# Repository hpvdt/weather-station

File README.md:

# weather-station
Weather station project

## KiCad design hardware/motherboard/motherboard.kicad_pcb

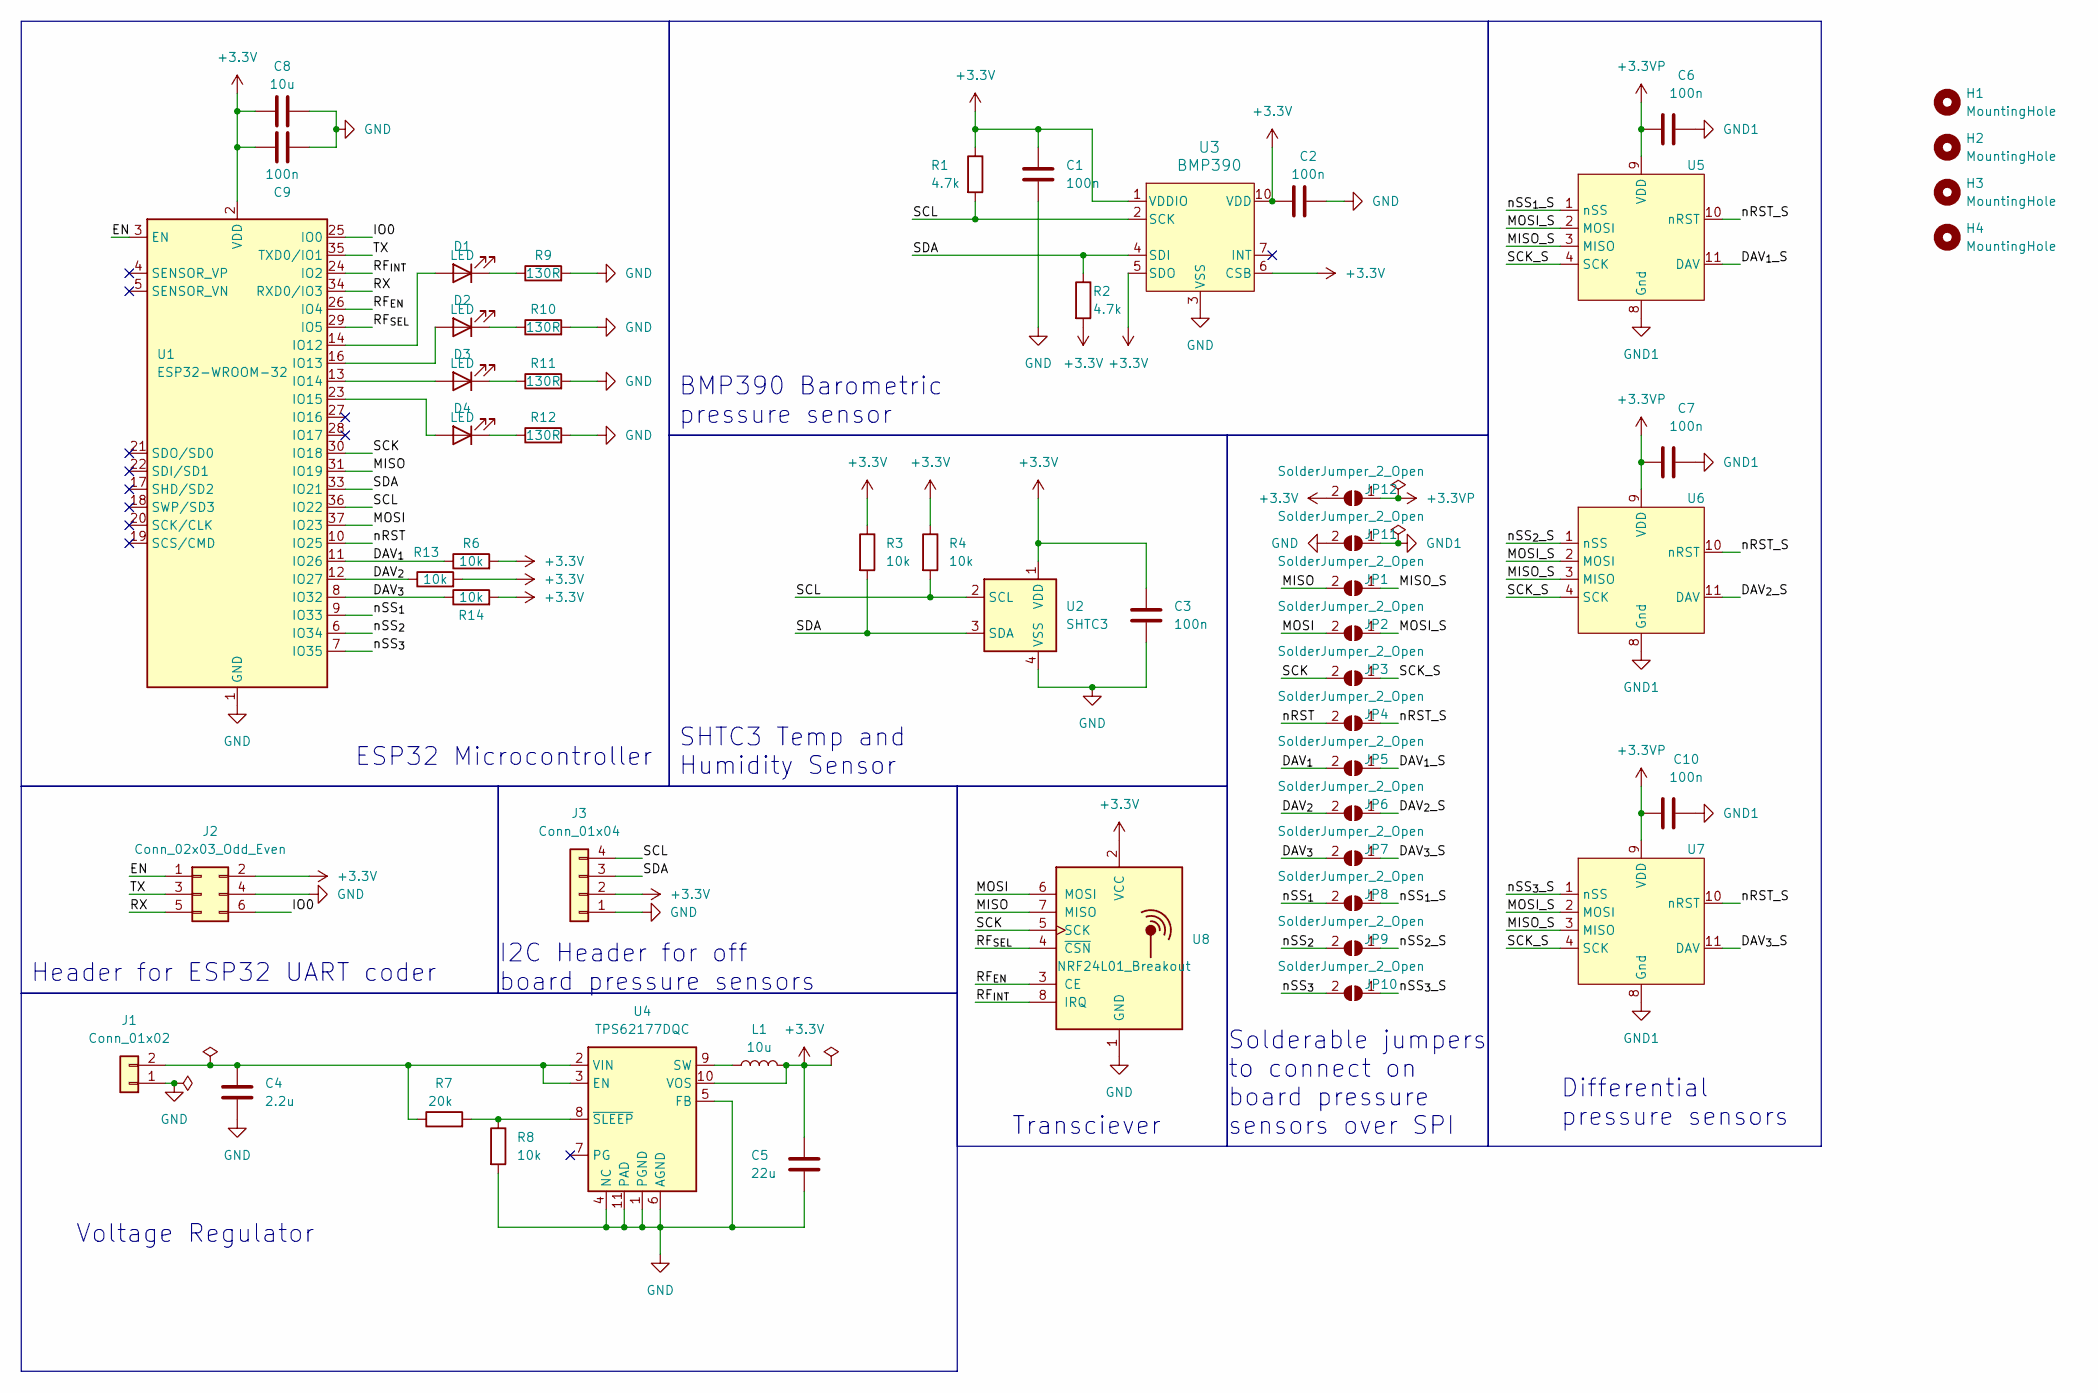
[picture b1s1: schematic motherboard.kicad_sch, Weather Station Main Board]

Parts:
C1, C2, C3, C6, C7, C9, C10: 100n; C_0603_1608Metric
C4: 2.2u; C_0603_1608Metric
C5: 22u; C_0805_2012Metric
C8: 10u; C_0805_2012Metric
D1, D2, D3, D4: LED; LED_0805_2012Metric
H1, H2, H3, H4: MountingHole; MountingHole_3mm
J1: Conn_01x02; AMASS_XT60-F_1x02_P7.20mm_Vertical
J2: Conn_02x03_Odd_Even; IDC-Header_2x03_P2.54mm_Vertical
J3: Conn_01x04; PinSocket_1x04_P2.54mm_Vertical
JP1, JP2, JP3, JP4, JP5, JP6, JP7, JP8, JP9, JP10, JP11, JP12: SolderJumper_2_Open; SolderJumper-2_P1.3mm_Open_RoundedPad1.0x1.5mm
L1: 10u; L_Taiyo-Yuden_MD-4040
R1, R2: 4.7k; R_0603_1608Metric
R3, R4, R6, R8, R13, R14: 10k; R_0603_1608Metric
R7: 20k; R_0603_1608Metric
R9, R10, R11, R12: 130R; R_0603_1608Metric
U1: ESP32-WROOM-32; ESP32-WROOM-32D
U2: SHTC3; Sensirion_DFN-4-1EP_2x2mm_P1mm_EP0.7x1.6mm
U3: BMP390; LGA10_BMP390_BOS
U4: TPS62177DQC; WSON-10-1EP_2x3mm_P0.5mm_EP0.84x2.4mm_ThermalVias
U5, U6, U7: HV120SM02C
U8: NRF24L01_Breakout; nRF24L01_Breakout

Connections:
+3.3V: C1.1, C2.1, C3.1, C5.1, C8.2, C9.2, J2.2, J3.2, JP12.2 (B), L1.2, R1.1, R2.2, R3.1, R4.1, R6.2, R13.2, R14.2, U1.2 (VDD), U2.1 (VDD), U3.1 (VDDIO), U3.5 (SDO), U3.6 (CSB), U3.10 (VDD), U4.10 (VOS), U8.2 (VCC)
+3.3VP: C6.1, C7.1, C10.1, JP12.1 (A), U5.9 (VDD), U6.9 (VDD), U7.9 (VDD)
/DAV_{1}: JP5.2 (B), R6.1, U1.11 (IO26)
/DAV_{1}_S: JP5.1 (A), U5.11 (DAV)
/DAV_{2}: JP6.2 (B), R13.1, U1.12 (IO27)
/DAV_{2}_S: JP6.1 (A), U6.11 (DAV)
/DAV_{3}: JP7.2 (B), R14.1, U1.8 (IO32)
/DAV_{3}_S: JP7.1 (A), U7.11 (DAV)
/EN: J2.1, U1.3 (EN)
/IO0: J2.6, U1.25 (IO0)
/MISO: JP1.2 (B), U1.31 (IO19), U8.7 (MISO)
/MISO_S: JP1.1 (A), U5.3 (MISO), U6.3 (MISO), U7.3 (MISO)
/MOSI: JP2.2 (B), U1.37 (IO23), U8.6 (MOSI)
/MOSI_S: JP2.1 (A), U5.2 (MOSI), U6.2 (MOSI), U7.2 (MOSI)
/RF_{EN}: U1.26 (IO4), U8.3 (CE)
/RF_{INT}: U1.24 (IO2), U8.8 (IRQ)
/RF_{SEL}: U1.29 (IO5), U8.4 (~CSN)
/RX: J2.5, U1.34 (RXD0/IO3)
/SCK: JP3.2 (B), U1.30 (IO18), U8.5 (SCK)
/SCK_S: JP3.1 (A), U5.4 (SCK), U6.4 (SCK), U7.4 (SCK)
/SCL: J3.4, R1.2, R4.2, U1.36 (IO22), U2.2 (SCL), U3.2 (SCK)
/SDA: J3.3, R2.1, R3.2, U1.33 (IO21), U2.3 (SDA), U3.4 (SDI)
/TX: J2.3, U1.35 (TXD0/IO1)
/nRST: JP4.2 (B), U1.10 (IO25)
/nRST_S: JP4.1 (A), U5.10 (nRST), U6.10 (nRST), U7.10 (nRST)
/nSS_{1}: JP8.2 (B), U1.9 (IO33)
/nSS_{1}_S: JP8.1 (A), U5.1 (nSS)
/nSS_{2}: JP9.2 (B), U1.6 (IO34)
/nSS_{2}_S: JP9.1 (A), U6.1 (nSS)
/nSS_{3}: JP10.2 (B), U1.7 (IO35)
/nSS_{3}_S: JP10.1 (A), U7.1 (nSS)
GND: C1.2, C2.2, C3.2, C4.2, C5.2, C8.1, C9.1, J1.1, J2.4, J3.1, JP11.2 (B), R8.2, R9.2, R10.2, R11.2, R12.2, U1.1 (GND), U1.15 (GND), U1.38 (GND), U1.39 (GND), U2.4 (VSS), U3.3 (VSS), U3.8 (VSS), U3.9 (VSS), U4.1 (PGND), U4.4 (NC), U4.5 (FB), U4.6 (AGND), U4.11 (PAD), U8.1 (GND)
GND1: C6.2, C7.2, C10.2, JP11.1 (A), U5.8 (Gnd), U6.8 (Gnd), U7.8 (Gnd)
unnamed: D1.2 (A), U1.14 (IO12)
unnamed: D1.1 (K), R9.1
unnamed: D2.2 (A), U1.16 (IO13)
unnamed: D2.1 (K), R10.1
unnamed: D3.2 (A), U1.13 (IO14)
unnamed: D3.1 (K), R11.1
unnamed: D4.2 (A), U1.23 (IO15)
unnamed: D4.1 (K), R12.1
unnamed: C4.1, J1.2, R7.1, U4.2 (VIN), U4.3 (EN)
unnamed: L1.1, U4.9 (SW)
unnamed: R7.2, R8.1, U4.8 (~SLEEP)

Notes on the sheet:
Header for ESP32 UART coder
I2C Header for off board pressure sensors
Transciever
ESP32 Microcontroller
Solderable jumpers to connect on board pressure sensors over SPI
Voltage Regulator
Differential pressure sensors
BMP390 Barometric pressure sensor
SHTC3 Temp and Humidity Sensor

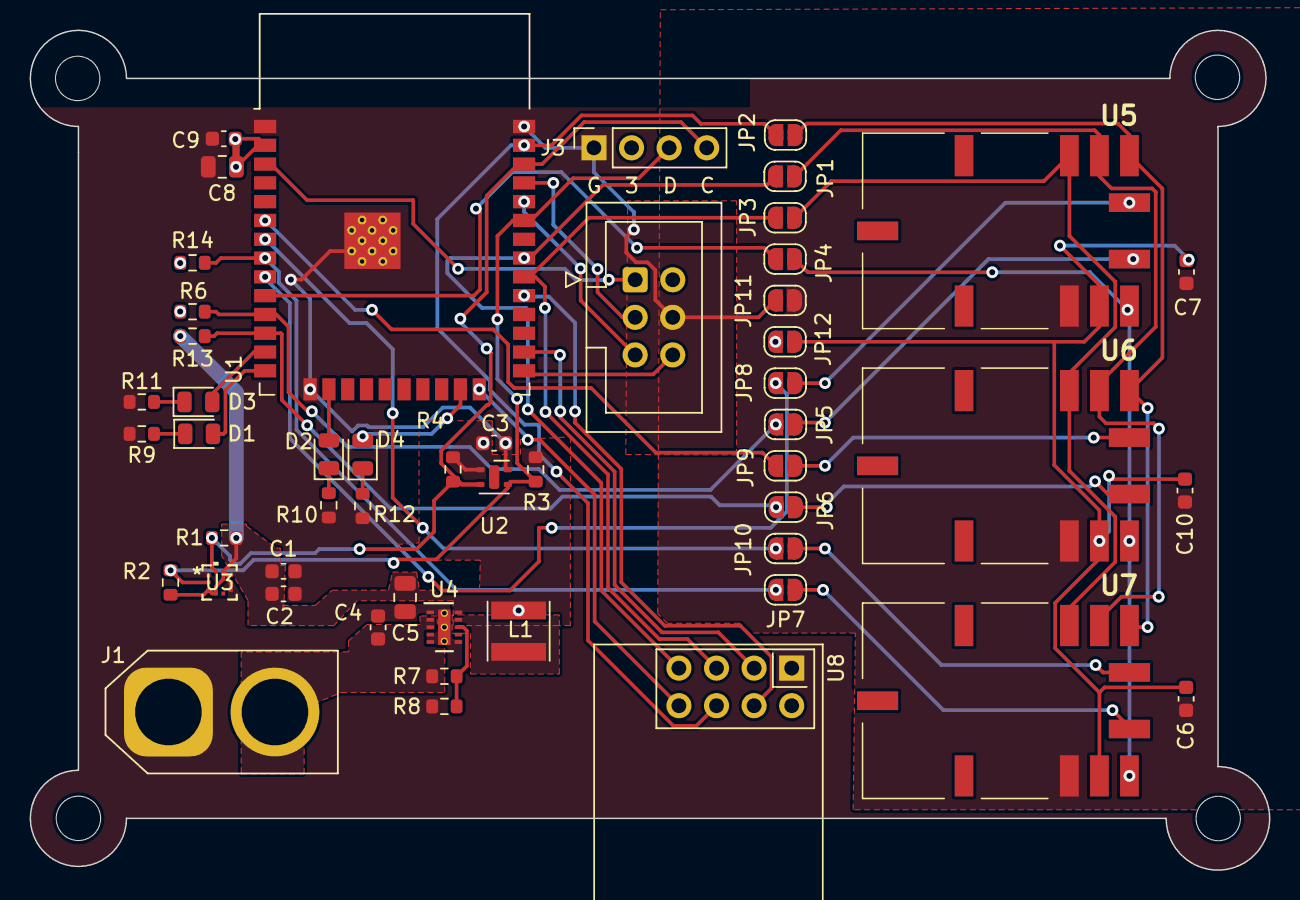
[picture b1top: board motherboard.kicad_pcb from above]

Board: 2 copper layers, 83.7 x 56.7 mm, 55 parts (0 on the bottom side), 44 nets.

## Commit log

2023-12-06 Initial Commit
    Uploading first schematic
2023-12-06 Added jumpers
    Added jumper connections to seperate pressure sensors unless soldered together
2023-12-06 Test commit to pull
2023-12-06 Updated gitignore
2023-12-06 On Board Pressure Sensors
    Rerouted on board pressure sensors for SPI with solderable breaks in connections. Added telemetry unit.
2023-12-06 Moved hardware files
    Moved hadware files to new "motherboard" project and added footprint for the ND005D complete with model.
2023-12-06 Added firmware folder
2023-12-06 Schematic with pressure sensors and transciever
    Set up schematic for I2C communication with off board pressure sensors or SPI communication with on board pressure sensors. Added transceiver. Formatted schematic. Added footprints for barometric pre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
2023-12-07 Power solder connections
    Added solder connections for power and ground because I forgot them last time and updated footprint assignments
2023-12-08 Completed schematic
    Completed schematic with all footprints assigned
2023-12-09 Initial PCB design
    Initial PCB design complete
2023-12-09 Finalized PCB design revision 1
2023-12-09 Hole change
2023-12-09 Removed Via bridge
    rerouted one trace to remove via bridge and keep it neatly on one layer
2023-12-10 Simpler power routing
    Added vias to connect power to flood on back layer rather than running traces on top layer
2023-12-10 Fixed Decoupling Capaciors for ESP32
2023-12-10 Fixed Clearance Issues
2023-12-12 Added ordered files
2023-12-12 Widened drill holes to 0.3mm
    Edited footprints for the ESP32 and the pressure sensor to increase the via widths to 0.3mm from 0.2mm to make them cheaper to produce
2023-12-19 BOM changes
2024-01-12 firmware inital commit
2024-01-18 Baseline blink
    Baseline system to blink one of the status LEDs on the weather station board.
    There is an issue with including the `BMP3XX` library at the present. Will need to investigate further or replace.
2024-01-18 ALL THE LEDs!!
2024-01-23 Bluetooth Sensor Test
2024-01-26 Working Website
2024-01-26 Working website after battery testing
2024-01-27 Updated Website with Dew Point calculation
2024-02-02 Updated files with air density calculations
